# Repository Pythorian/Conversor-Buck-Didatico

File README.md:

# Conversor-Buck-Didatico
 Este trabalho é um conversor Buck desenvolvido para ajudar nas aulas de Eletrônica de Potência e Controle Digital.

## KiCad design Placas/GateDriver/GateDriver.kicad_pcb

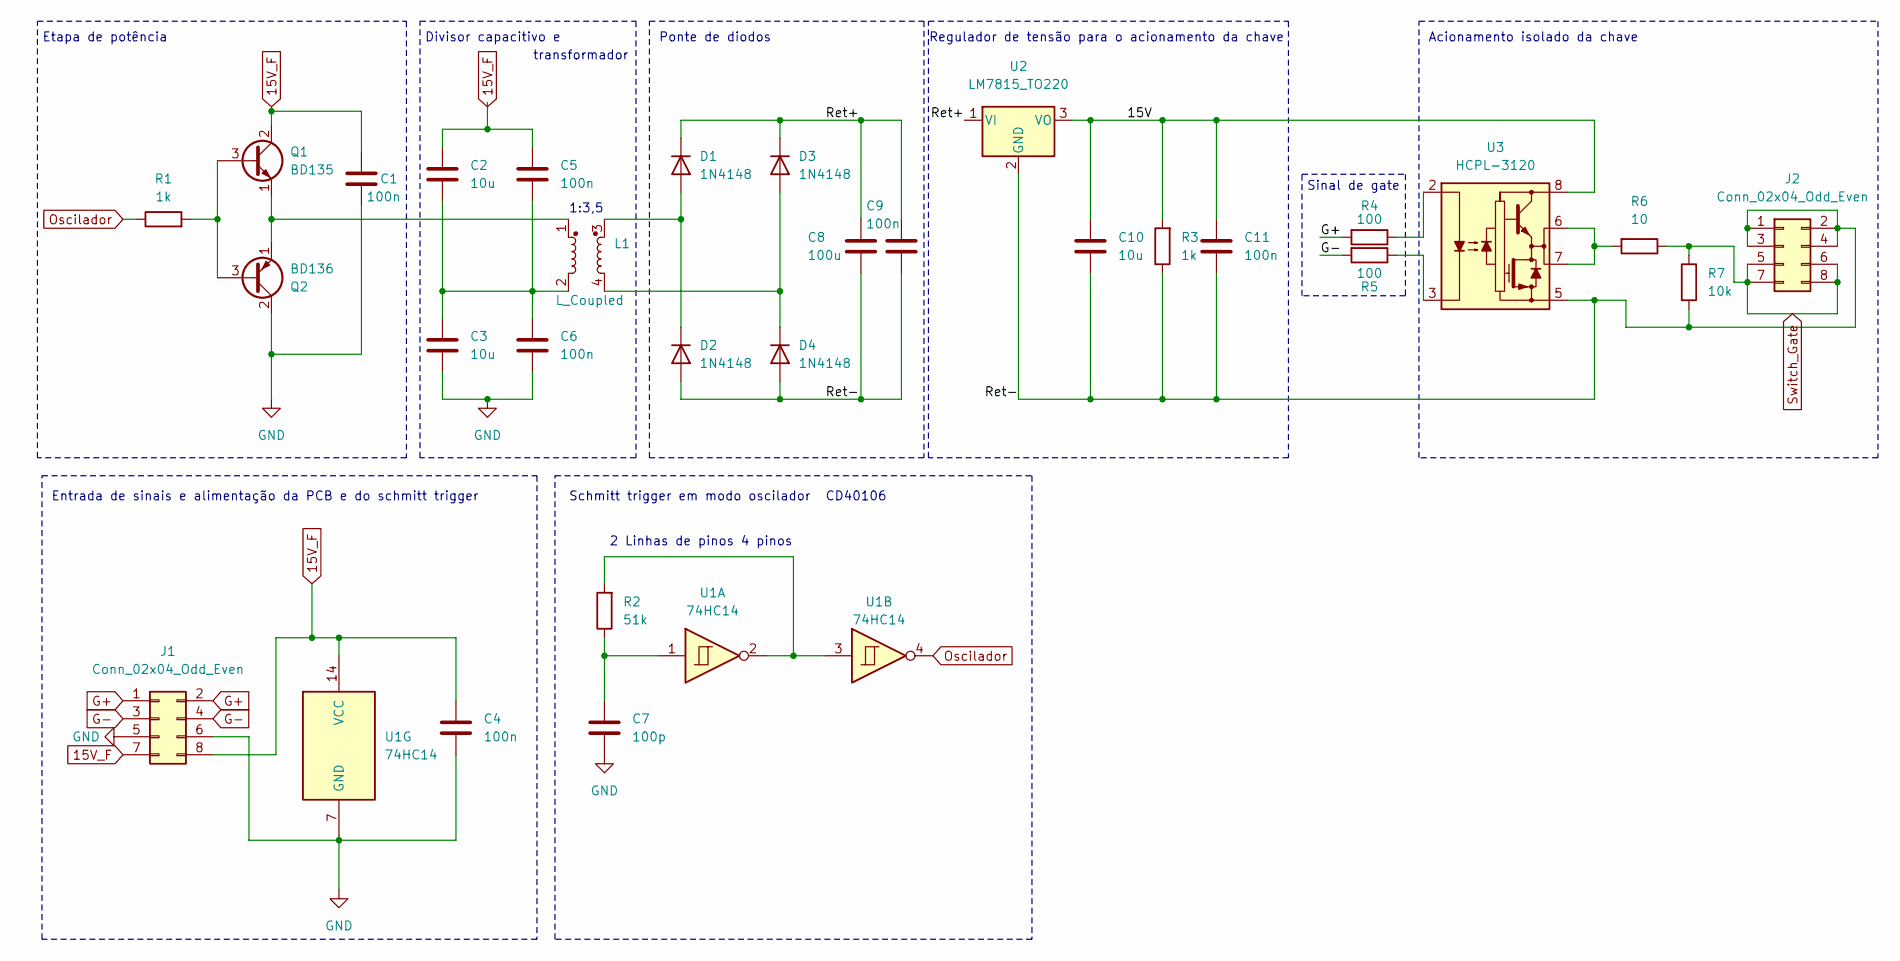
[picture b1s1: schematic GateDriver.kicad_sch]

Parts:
C1, C4, C5, C6, C9, C11: 100n; C_Disc_D5.0mm_W2.5mm_P5.00mm
C2, C3, C10: 10u; CP_Radial_D5.0mm_P2.00mm
C7: 100p; C_Disc_D5.0mm_W2.5mm_P5.00mm
C8: 100u; CP_Radial_D8.0mm_P3.50mm
D1, D2, D3, D4: 1N4148; D_DO-35_SOD27_P7.62mm_Horizontal
J1, J2: Conn_02x04_Odd_Even; PinHeader_2x04_P2.54mm_Horizontal
L1: L_Coupled; Inductor_Coupled
Q1: BD135; TO-126-3_Vertical
Q2: BD136; TO-126-3_Vertical
R1, R3: 1k; R_Axial_DIN0204_L3.6mm_D1.6mm_P7.62mm_Horizontal
R2: 51k; R_Axial_DIN0204_L3.6mm_D1.6mm_P7.62mm_Horizontal
R4, R5: 100; R_Axial_DIN0204_L3.6mm_D1.6mm_P7.62mm_Horizontal
R6: 10; R_Axial_DIN0204_L3.6mm_D1.6mm_P7.62mm_Horizontal
R7: 10k; R_Axial_DIN0204_L3.6mm_D1.6mm_P7.62mm_Horizontal
U1: 74HC14; DIP-14_W7.62mm_Socket
U2: LM7815_TO220; TO-220-3_Vertical
U3: HCPL-3120; DIP-8_W7.62mm_Socket

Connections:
15V_F: C1.1, C2.1, C4.1, C5.1, J1.7, J1.8, Q1.2 (C), U1.14 (VCC)
/15V: C10.1, C11.1, R3.2, U2.3 (VO), U3.8 (VCC)
/Ret+: C8.1, C9.1, D1.1 (K), D3.1 (K), U2.1 (VI)
/Ret-: C8.2, C9.2, C10.2, C11.2, D2.2 (A), D4.2 (A), J2.1, J2.2, J2.3, J2.4, R3.1, R7.2, U2.2 (GND), U3.5 (VEE)
G+: J1.1, J1.2, R4.2
G-: J1.3, J1.4, R5.2
GND: C1.2, C3.2, C4.2, C6.2, C7.2, J1.5, J1.6, Q2.2 (C), U1.7 (GND)
unnamed: C2.2, C3.1, C5.2, C6.1, L1.2
unnamed: C7.1, R2.1, U1.1
unnamed: D1.2 (A), D2.1 (K), L1.3
unnamed: D3.2 (A), D4.1 (K), L1.4
unnamed: Q1.3 (B), Q2.3 (B), R1.2
unnamed: L1.1, Q1.1 (E), Q2.1 (E)
unnamed: R2.2, U1.2, U1.3
unnamed: R6.2, U3.6 (VO), U3.7 (VO)
unnamed: R4.1, U3.2 (A)
unnamed: R5.1, U3.3 (C)
Oscilador: R1.1, U1.4
Switch_Gate: J2.5, J2.6, J2.7, J2.8, R6.1, R7.1

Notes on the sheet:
CD40106
transformador
1:3,5
Etapa de potência
Acionamento isolado da chave
Entrada de sinais e alimentação da PCB e do schmitt trigger
Divisor capacitivo e
Ponte de diodos
Schmitt trigger em modo oscilador
Sinal de gate
Regulador de tensão para o acionamento da chave
2 Linhas de pinos 4 pinos

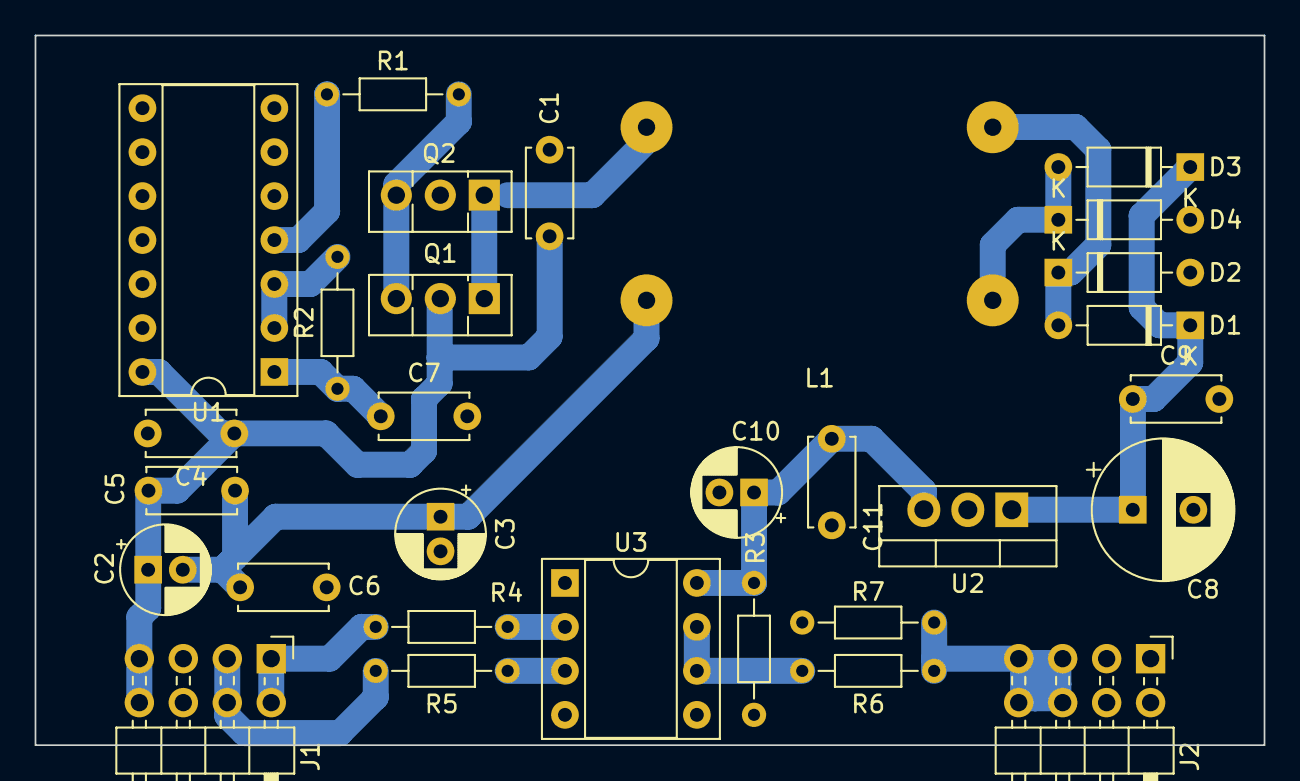
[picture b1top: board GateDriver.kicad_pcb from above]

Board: 2 copper layers, 71.0 x 41.0 mm, 30 parts (0 on the bottom side), 19 nets.

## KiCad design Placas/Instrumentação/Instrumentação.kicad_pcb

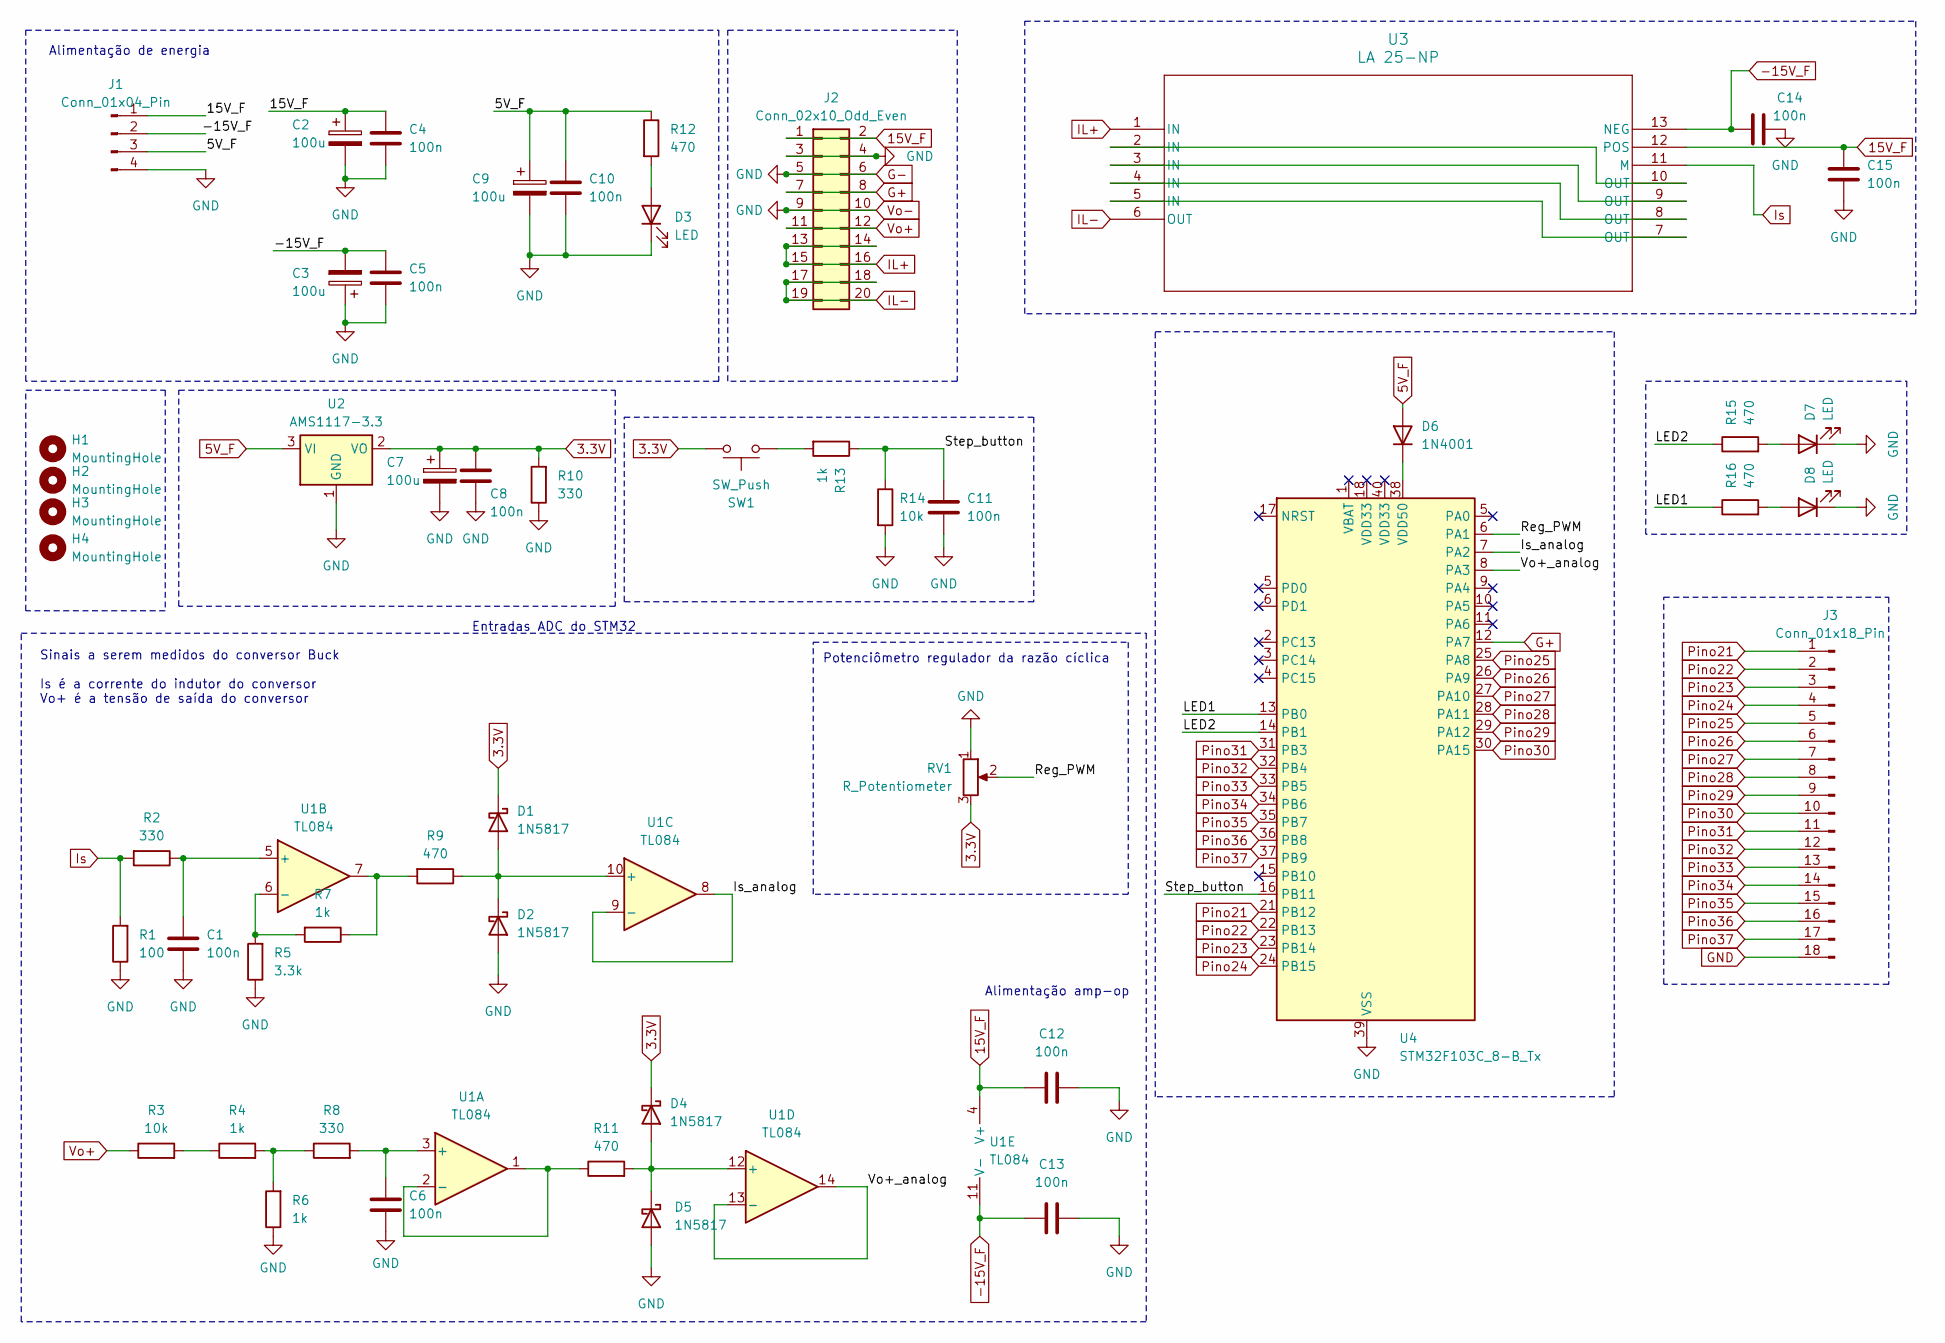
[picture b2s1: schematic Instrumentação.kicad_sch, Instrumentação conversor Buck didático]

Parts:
C1, C4, C5, C6, C8, C10, C11, C12, C13, C14, C15: 100n; C_Disc_D5.0mm_W2.5mm_P5.00mm
C2, C3, C7, C9: 100u; CP_Radial_D6.3mm_P2.50mm
D1, D2, D4, D5: 1N5817; D_DO-41_SOD81_P10.16mm_Horizontal
D3, D7, D8: LED; LED_D3.0mm
D6: 1N4001; D_DO-41_SOD81_P10.16mm_Horizontal
H1, H2, H3, H4: MountingHole; Furo
J1: Conn_01x04_Pin; Molex_KK-254_AE-6410-04A_1x04_P2.54mm_Vertical
J2: Conn_02x10_Odd_Even; PinHeader_2x10_P2.54mm_Horizontal
J3: Conn_01x18_Pin; PinHeader_1x18_P2.54mm_Vertical
R1: 100; R_Axial_DIN0204_L3.6mm_D1.6mm_P7.62mm_Horizontal
R2, R8, R10: 330; R_Axial_DIN0204_L3.6mm_D1.6mm_P7.62mm_Horizontal
R3, R14: 10k; R_Axial_DIN0204_L3.6mm_D1.6mm_P7.62mm_Horizontal
R4, R6, R7, R13: 1k; R_Axial_DIN0204_L3.6mm_D1.6mm_P7.62mm_Horizontal
R5: 3.3k; R_Axial_DIN0204_L3.6mm_D1.6mm_P7.62mm_Horizontal
R9, R11, R12, R15, R16: 470; R_Axial_DIN0204_L3.6mm_D1.6mm_P7.62mm_Horizontal
RV1: R_Potentiometer; Potentiometer_Alps_RK163_Single_Horizontal
SW1: SW_Push; SW_PUSH_6mm
U1: TL084; DIP-14_W7.62mm_Socket
U2: AMS1117-3.3; SOT-223-3_TabPin2
U3: LA 25-NP; LA 25-NP_LEM
U4: STM32F103C_8-B_Tx; DIP-40_W15.24mm_Socket_LongPads

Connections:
3.3V: C7.1, C8.2, D1.1 (K), D4.1 (K), R10.2, RV1.3, SW1.2, U2.2 (VO)
5V_F: C9.1, C10.2, D6.2 (A), J1.3, R12.1, U2.3 (VI)
15V_F: C2.1, C4.2, C12.1, C15.2, J1.1, J2.1, J2.2, U1.4 (V+), U3.12 (POS)
-15V_F: C3.2, C5.2, C13.1, C14.2, J1.2, U1.11 (V-), U3.13 (NEG)
/Is_analog: U1.8, U1.9 (-), U4.7 (PA2)
/LED1: R16.1, U4.13 (PB0)
/LED2: R15.1, U4.14 (PB1)
/Reg_PWM: RV1.2, U4.6 (PA1)
/Step_button: C11.2, R13.1, R14.1, U4.16 (PB11)
/Vo+_analog: U1.13 (-), U1.14, U4.8 (PA3)
G+: J2.7, J2.8, U4.12 (PA7)
G-: C1.1, C2.2, C3.1, C4.1, C5.1, C6.1, C7.2, C8.1, C9.2, C10.1, C11.1, C12.2, C13.2, C14.1, C15.1, D2.2 (A), D3.1 (K), D5.2 (A), D7.1 (K), D8.1 (K), J1.4, J2.3, J2.4, J2.5, J2.6, J2.9, J2.10, J3.18, R1.1, R5.1, R6.1, R10.1, R14.2, RV1.1, U2.1 (GND), U4.19 (VSS), U4.20 (VSS), U4.39 (VSS)
IL+: J2.13, J2.14, J2.15, J2.16, U3.1 (IN)
IL-: J2.17, J2.18, J2.19, J2.20, U3.6 (OUT)
Is: R1.2, R2.2, U3.11 (M)
unnamed: D1.2 (A), D2.1 (K), R9.1, U1.10 (+)
unnamed: D3.2 (A), R12.2
unnamed: D4.2 (A), D5.1 (K), R11.2, U1.12 (+)
unnamed: D6.1 (K), U4.38 (VDD50)
unnamed: D7.2 (A), R15.2
unnamed: D8.2 (A), R16.2
unnamed: R3.2, R4.1
unnamed: R4.2, R6.2, R8.1
unnamed: R7.1, R9.2, U1.7
unnamed: R13.2, SW1.1
unnamed: C6.2, R8.2, U1.3 (+)
unnamed: R11.1, U1.1, U1.2 (-)
unnamed: C1.2, R2.1, U1.5 (+)
unnamed: R5.2, R7.2, U1.6 (-)
unnamed: U3.2 (IN), U3.10 (OUT)
unnamed: U3.3 (IN), U3.9 (OUT)
unnamed: U3.4 (IN), U3.8 (OUT)
unnamed: U3.5 (IN), U3.7 (OUT)
Pino21: J3.1, U4.21 (PB12)
Pino22: J3.2, U4.22 (PB13)
Pino23: J3.3, U4.23 (PB14)
Pino24: J3.4, U4.24 (PB15)
Pino25: J3.5, U4.25 (PA8)
Pino26: J3.6, U4.26 (PA9)
Pino27: J3.7, U4.27 (PA10)
Pino28: J3.8, U4.28 (PA11)
Pino29: J3.9, U4.29 (PA12)
Pino30: J3.10, U4.30 (PA15)
Pino31: J3.11, U4.31 (PB3)
Pino32: J3.12, U4.32 (PB4)
Pino33: J3.13, U4.33 (PB5)
Pino34: J3.14, U4.34 (PB6)
Pino35: J3.15, U4.35 (PB7)
Pino36: J3.16, U4.36 (PB8)
Pino37: J3.17, U4.37 (PB9)
Vo+: J2.11, J2.12, R3.1

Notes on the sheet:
Alimentação de energia
Potenciômetro regulador da razão cíclica
Sinais a serem medidos do conversor Buck Is é a corrente do indutor do conversor Vo+ é a tensão de saída do conversor
Entradas ADC do STM32
Alimentação amp-op

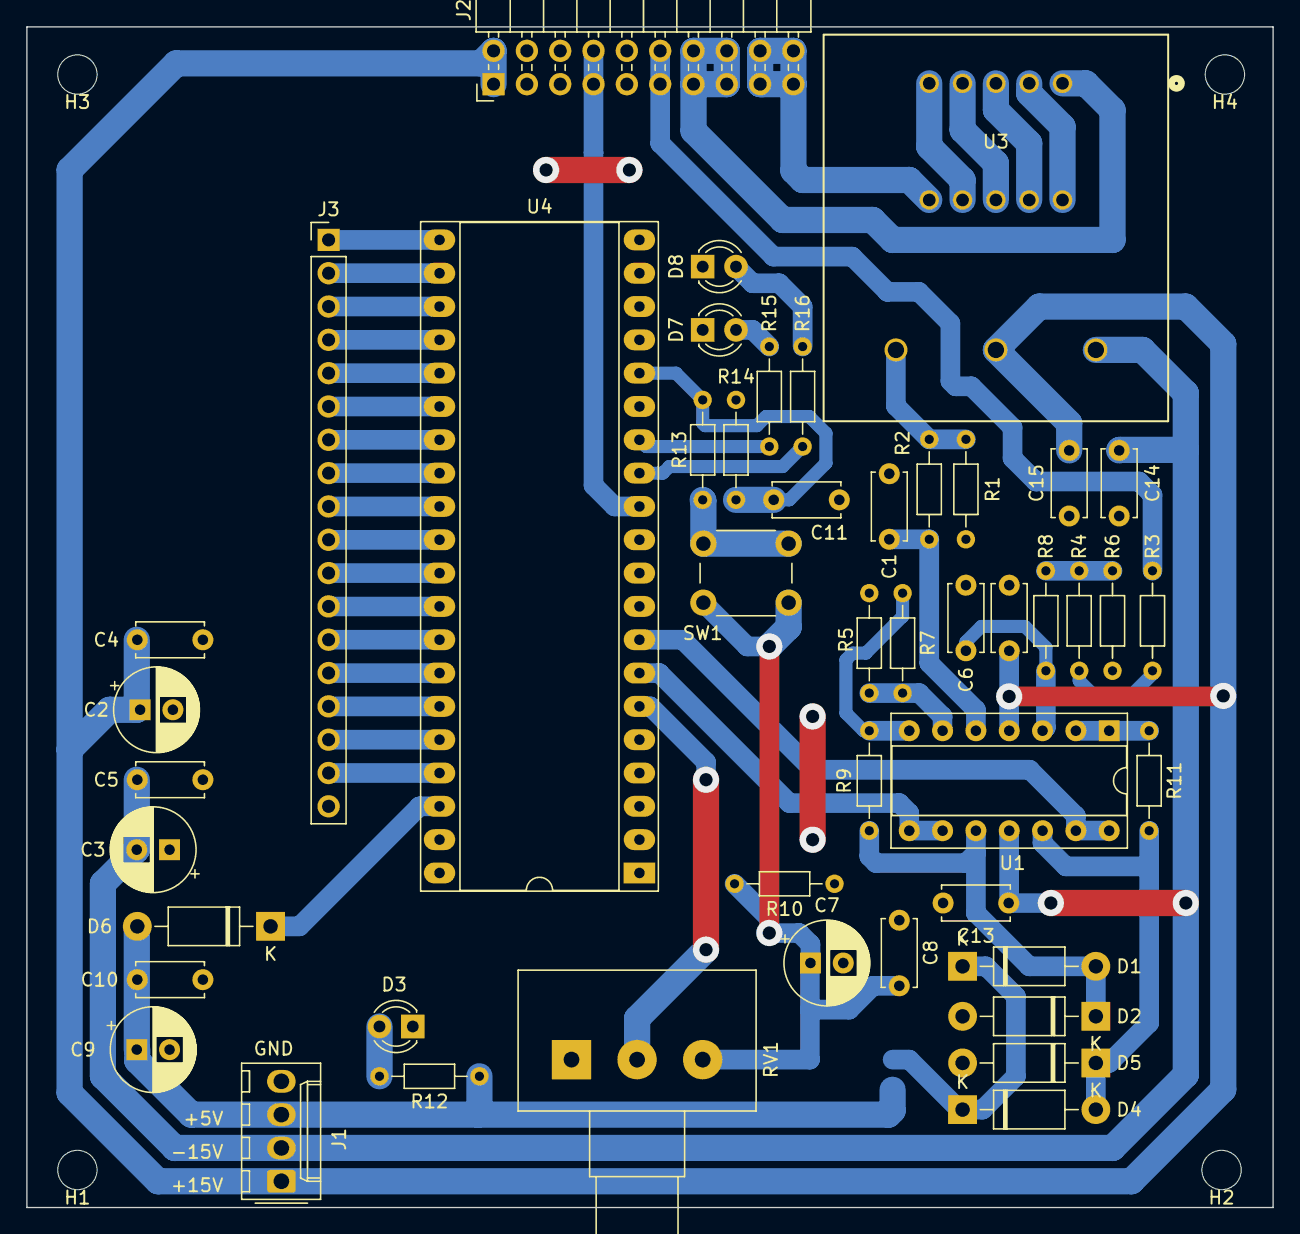
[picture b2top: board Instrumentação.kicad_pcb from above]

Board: 2 copper layers, 95.0 x 90.0 mm, 52 parts (1 on the bottom side), 51 nets.

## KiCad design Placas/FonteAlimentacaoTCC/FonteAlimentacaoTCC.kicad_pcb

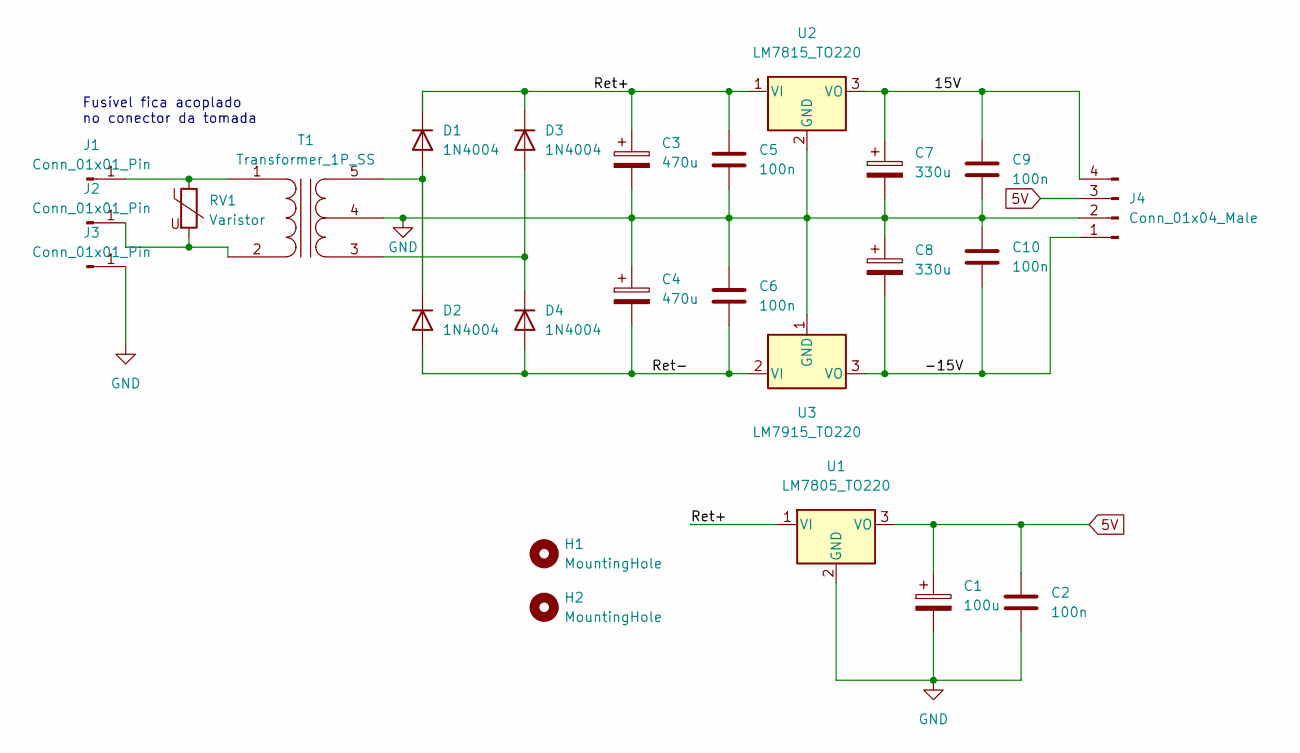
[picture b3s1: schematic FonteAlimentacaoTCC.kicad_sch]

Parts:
C1: 100u; CP_Radial_D8.0mm_P3.50mm
C2, C5, C6, C9, C10: 100n; C_Disc_D5.0mm_W2.5mm_P5.00mm
C3, C4: 470u; CP_Radial_D13.0mm_P5.00mm
C7, C8: 330u; CP_Radial_D10.0mm_P5.00mm
D1, D2, D3, D4: 1N4004; D_DO-41_SOD81_P10.16mm_Horizontal
H1, H2: MountingHole; parafuso
J1, J2, J3: Conn_01x01_Pin; entrada
J4: Conn_01x04_Male; conector_saida
RV1: Varistor; RV_Disc_D9mm_W3.3mm_P5mm
T1: Transformer_1P_SS; transformador
U1: LM7805_TO220; TO-220-3_Vertical
U2: LM7815_TO220; TO-220-3_Vertical
U3: LM7915_TO220; TO-220-3_Vertical

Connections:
5V: C1.1, C2.1, J4.3, U1.3 (VO)
/15V: C7.1, C9.1, J4.4, U2.3 (VO)
/-15V: C8.2, C10.2, J4.1, U3.3 (VO)
/Ret+: C3.1, C5.1, D1.1 (K), D3.1 (K), U1.1 (VI), U2.1 (VI)
/Ret-: C4.2, C6.2, D2.2 (A), D4.2 (A), U3.2 (VI)
GND: C1.2, C2.2, C3.2, C4.1, C5.2, C6.1, C7.2, C8.1, C9.2, C10.1, J3.1, J4.2, T1.4 (SC), U1.2 (GND), U2.2 (GND), U3.1 (GND)
unnamed: D1.2 (A), D2.1 (K), T1.5 (SB)
unnamed: D3.2 (A), D4.1 (K), T1.3 (SA)
unnamed: J1.1, RV1.1, T1.1 (AA)
unnamed: J2.1, RV1.2, T1.2 (AB)

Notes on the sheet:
Fusível fica acoplado no conector da tomada

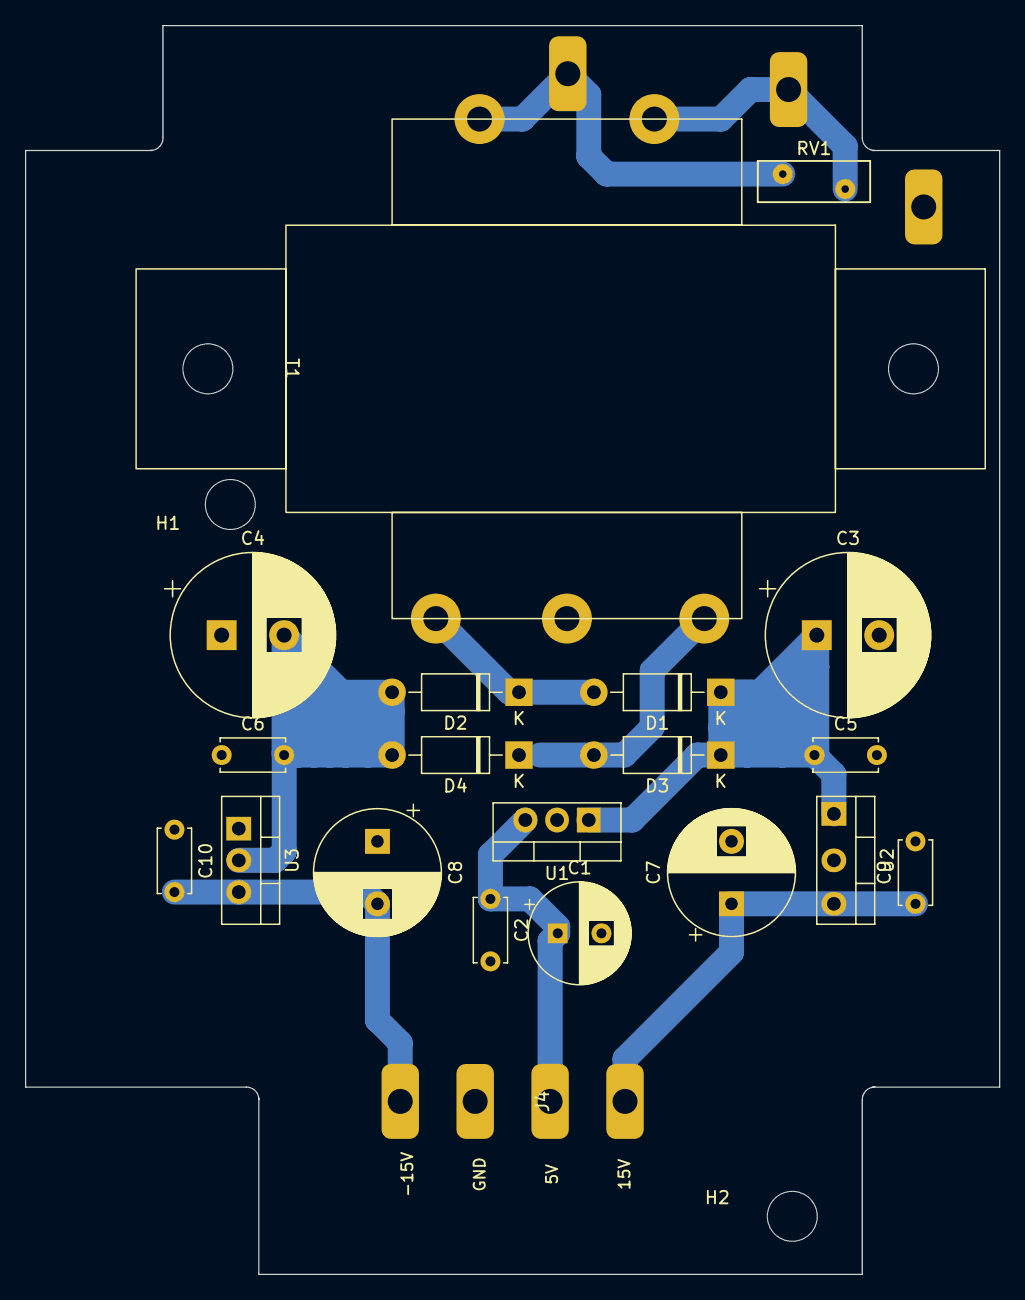
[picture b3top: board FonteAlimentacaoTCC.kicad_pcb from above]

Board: 2 copper layers, 78.0 x 100.0 mm, 25 parts (0 on the bottom side), 10 nets.

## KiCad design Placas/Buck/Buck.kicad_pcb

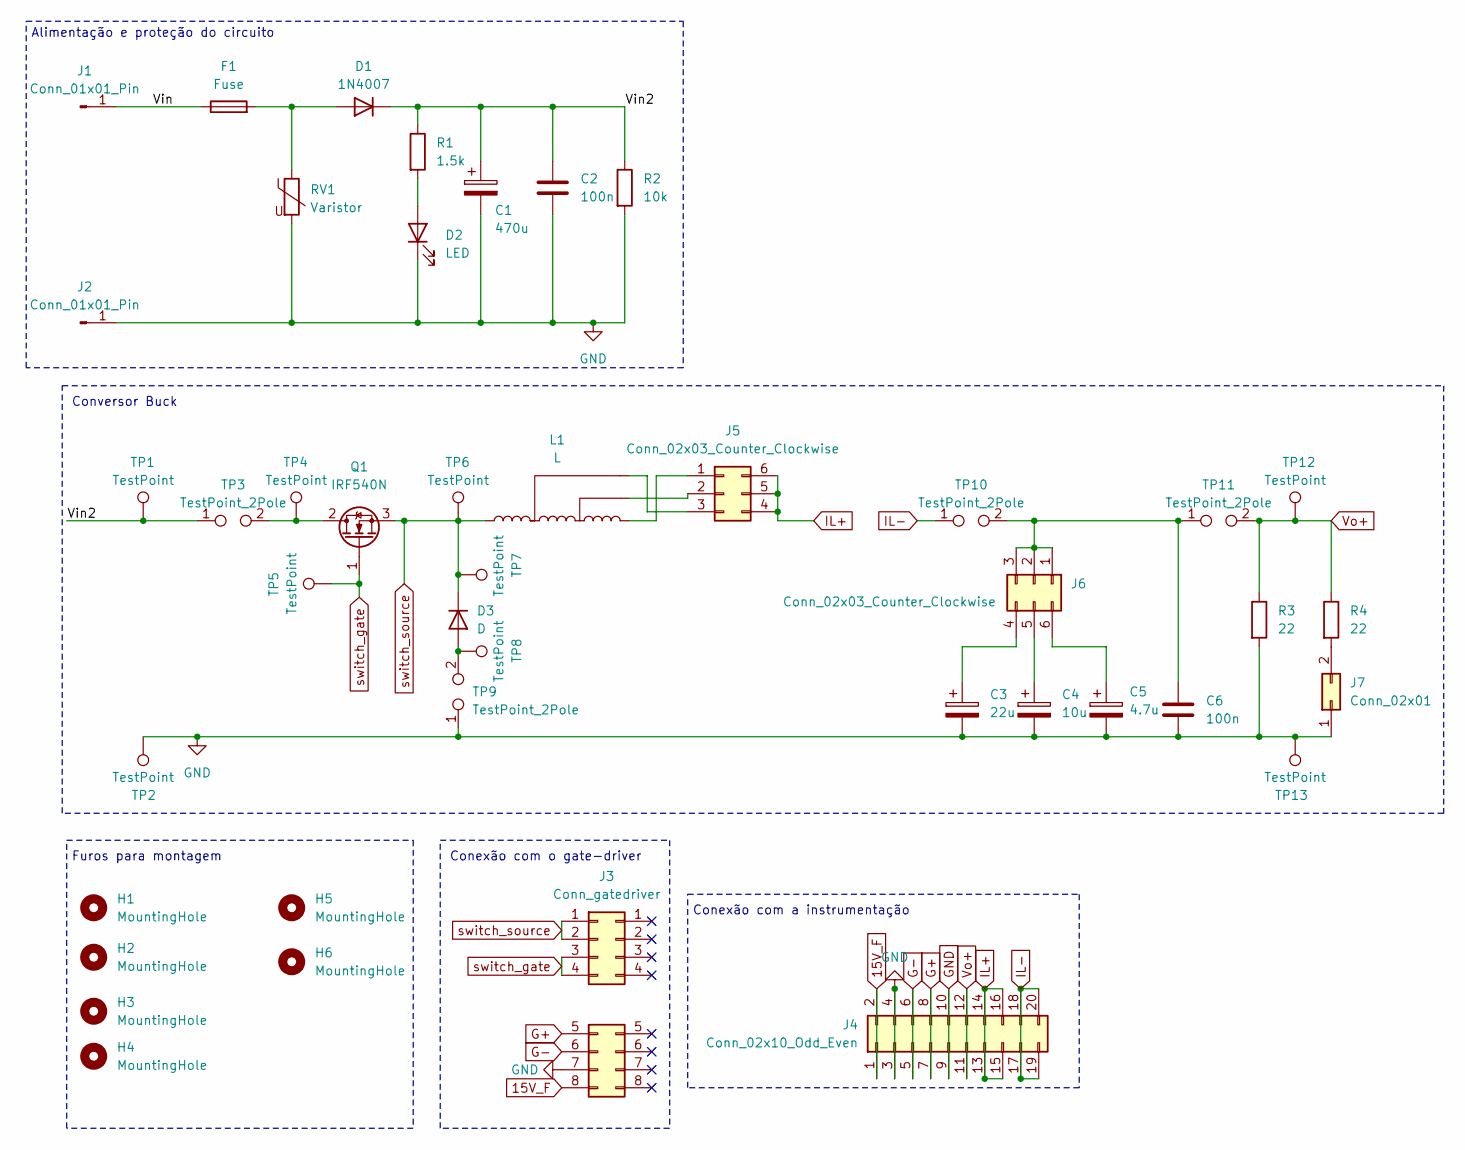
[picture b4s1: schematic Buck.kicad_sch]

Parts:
C1: 470u; CP_Radial_D16.0mm_P7.50mm
C2, C6: 100n; C_Disc_D5.0mm_W2.5mm_P5.00mm
C3: 22u; CP_Radial_D6.3mm_P2.50mm
C4: 10u; CP_Radial_D5.0mm_P2.00mm
C5: 4.7u; CP_Radial_D5.0mm_P2.00mm
D1: 1N4007; D_DO-41_SOD81_P10.16mm_Horizontal
D2: LED; LED_D3.0mm
D3: D; TO-220-2_Horizontal_TabDown
F1: Fuse
H1, H2, H3, H4, H5, H6: MountingHole; Furo
J1, J2: Conn_01x01_Pin; Banana_Jack_1Pin
J3: Conn_gatedriver; GateDriver
J4: Conn_02x10_Odd_Even; PinSocket_2x10_P2.54mm_Horizontal
J5, J6: Conn_02x03_Counter_Clockwise; PinHeader_2x03_P2.54mm_Vertical
J7: Conn_02x01; PinHeader_2x02_P2.54mm_Vertical
L1: L; Inductor_buck
Q1: IRF540N; TO-220-3_Horizontal_TabDown
R1: 1.5k; R_Axial_DIN0204_L3.6mm_D1.6mm_P7.62mm_Horizontal
R2: 10k; R_Axial_DIN0204_L3.6mm_D1.6mm_P7.62mm_Horizontal
R3, R4: 22; R_Axial_Power_L38.0mm_W9.0mm_P45.72mm
RV1: Varistor; RV_Disc_D7mm_W3.4mm_P5mm
TP1, TP2, TP4, TP5, TP6, TP7, TP8, TP12, TP13: TestPoint; TestPoint_Loop_D2.60mm_Drill1.6mm_Beaded
TP3, TP9, TP10, TP11: TestPoint_2Pole; Testpoint_current

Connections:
15V_F: J3.8 (Pin_15), J4.1, J4.2
G+: J3.5 (Pin_9), J4.7, J4.8
G-: J3.6 (Pin_11), J4.5, J4.6
GND: C1.2, C2.2, C3.2, C4.2, C5.2, C6.2, D2.1 (K), J2.1, J3.7 (Pin_13), J4.3, J4.4, J4.9, J4.10, J7.1, R2.2, R3.2, RV1.2, TP2.1, TP9.1, TP13.1; also elsewhere on the board
IL+: J4.13, J4.14, J4.15, J4.16, J5.4, J5.5, J5.6
IL-: J4.17, J4.18, J4.19, J4.20, TP10.1
unnamed: D1.2 (A), F1.2, RV1.1
unnamed 7: C1.1, C2.1, D1.1 (K), R1.1, R2.1, TP1.1, TP3.1; also elsewhere on the board
unnamed: D2.2 (A), R1.2
unnamed: D3.2 (A), TP8.1, TP9.2
unnamed: F1.1, J1.1
unnamed: J5.1, L1.4
unnamed: J5.2, L1.3
unnamed: J5.3, L1.2
unnamed: C6.1, J6.1, J6.2, J6.3, TP10.2, TP11.1
unnamed: C3.1, J6.4
unnamed: C4.1, J6.5
unnamed: C5.1, J6.6
unnamed 18: J7.2, R4.2; also elsewhere on the board
unnamed: Q1.2 (D), TP3.2, TP4.1
Vo+: J4.11, J4.12, R3.1, R4.1, TP11.2, TP12.1; also elsewhere on the board
switch_gate: J3.3 (Pin_5), J3.4 (Pin_7), Q1.1 (G), TP5.1
switch_source: D3.1 (K), J3.1, J3.2 (Pin_3), L1.1, Q1.3 (S), TP6.1, TP7.1

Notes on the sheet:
Conversor Buck
Conexão com o gate-driver
Alimentação e proteção do circuito
Furos para montagem
Conexão com a instrumentação

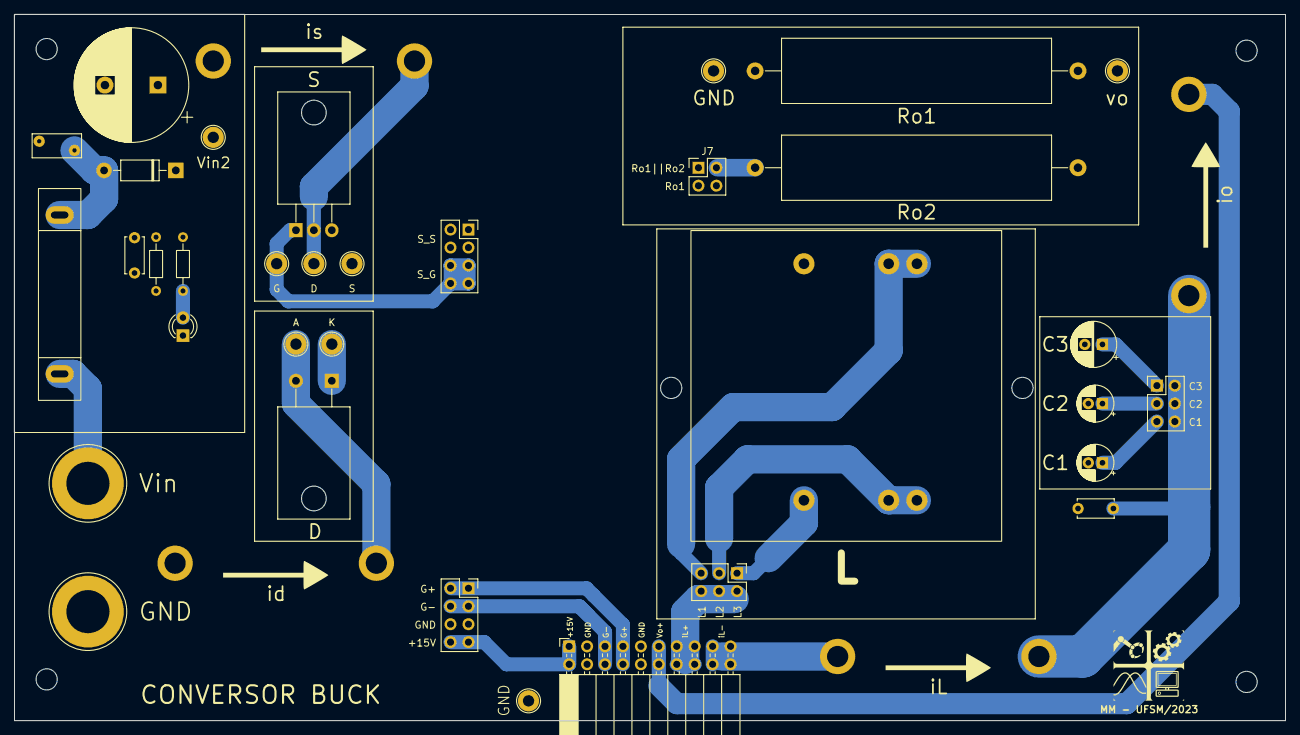
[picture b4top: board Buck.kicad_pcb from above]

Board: 2 copper layers, 180.0 x 100.0 mm, 43 parts (0 on the bottom side), 23 nets.

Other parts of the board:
Ro1, Ro2: 22; R_Axial_Power_L38.0mm_W9.0mm_P45.72mm
Vin2: TestPoint; TestPoint_Loop_D2.60mm_Drill1.6mm_Beaded

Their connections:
GND: Ro1.2; also elsewhere on the board
unnamed 7: Vin2.1; also elsewhere on the board
unnamed 18: Ro2.2; also elsewhere on the board
Vo+: Ro1.1, Ro2.1; also elsewhere on the board

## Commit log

2024-04-08 Alterando o arquivo matlab para a última versão.
2024-04-08 Imagens dos resultados em malha aberta do conversor.
2024-04-12 Atualização0.1
2024-05-31 Working
2024-06-04 CubeIDE main.c upload
2024-06-06 versão pré defesa
